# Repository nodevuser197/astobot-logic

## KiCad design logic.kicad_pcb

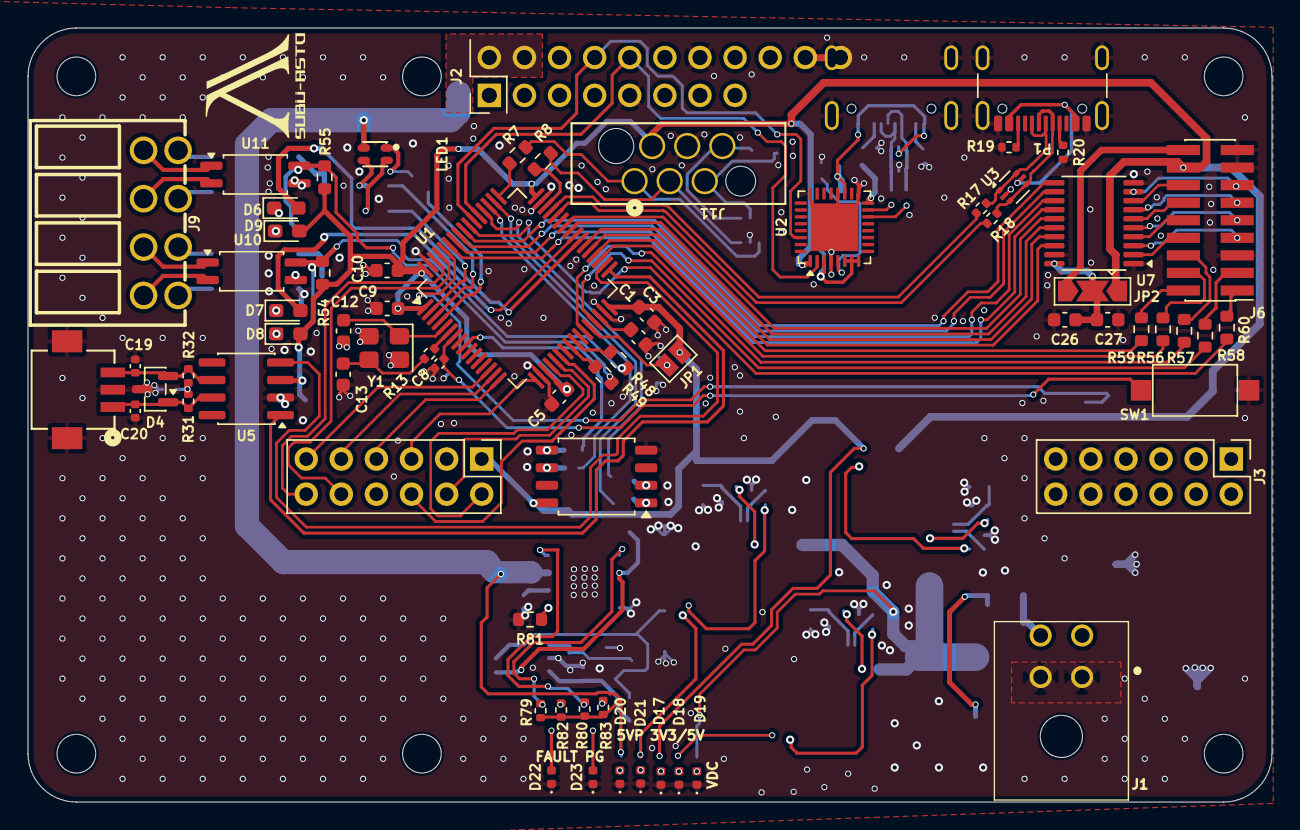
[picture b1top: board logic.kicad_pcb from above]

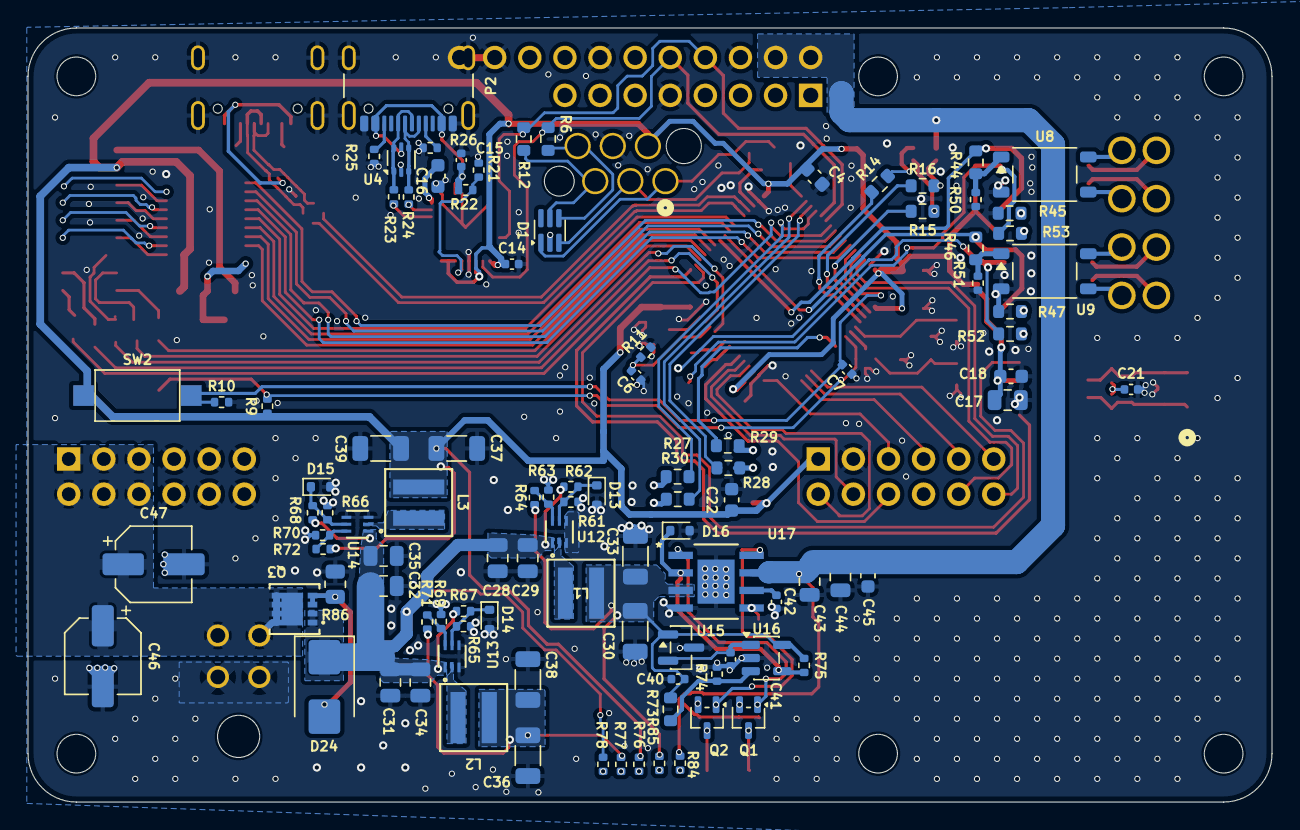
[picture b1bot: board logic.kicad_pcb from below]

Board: 2 copper layers, 90.0 x 56.0 mm, 169 parts (100 on the bottom side), 140 nets.

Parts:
C1, C3, C4, C10: 2u2; C_0603_1608Metric
C5, C9, C18, C26: u1; C_0603_1608Metric
C6, C7, C8, C15, C40, C41: u1; C_0402_1005Metric
C12, C13: 15p; C_0603_1608Metric
C14: 1u; C_0402_1005Metric
C16, C22, C27: 1u; C_0603_1608Metric
C17: 2.2u; C_0805_2012Metric
C19, C20: 47p; C_0402_1005Metric
C21: 2u2; C_0402_1005Metric
C28, C31, C32: 15u; C_0805_2012Metric
C29, C34, C35: 6.8u; C_0805_2012Metric
C30, C33, C36, C37, C38, C39: 33u; C_1206_3216Metric
C42: 22n; C_0402_1005Metric
C43, C44: 4u7; C_0805_2012Metric
C45: u22; C_0603_1608Metric
C46: 10u; CP_Elec_5x5.4
C47: 22u; CP_Elec_5x5.4
D1: SP0504BAHT; SOT-363_SC-70-6
D4: TVS-DUAL; SOT-23
D6, D7, D8, D9: Red; LED_0603_1608Metric_Pad1.05x0.95mm_HandSolder
D13, D14, D15: 5.1; D_SOD-523
D16: 5.1V; D_SOD-523
D17, D18: BLUE; LED_0402_1005Metric
D19, D20, D22: RED; LED_0402_1005Metric
D21, D23: GREEN; LED_0402_1005Metric
D24: SMBJ26; D_SMB
J1: CN; 66200421022
J2: Raspberry_Pi_4; PinHeader_2x20_P2.54mm_Vertical
J3: PWR; PinHeader_2x06_P2.54mm_Vertical
J4: Logic; PinHeader_2x06_P2.54mm_Vertical
J5: Conn_01x03; DF13A-3P-1-25H-21-
J6: Conn_02x09_Odd_Even; PinHeader_2x09_P1.27mm_Vertical_SMD
J9: ISI/O; JL15EDGRHC-35004B02
J11: Debug; CONN6_490107670612_WRE
JP1: SJ; SolderJumper-2_P1.3mm_Open_Pad1.0x1.5mm
JP2: SJ; SolderJumper-3_P2.0mm_Open_TrianglePad1.0x1.5mm
L1, L2, L3: 3.3u; IND_EXLA-0402_EAT
LED1: LTST-C19HE1WT_C458749; LTST-C19HE1WT
P1, P2: USB_C_Plug_USB2.0; USB_C_Receptacle_GCT_USB4105-xx-A_16P_TopMnt_Horizontal
Q1, Q2: MMBTA94; SOT-323_SC-70
Q3: DMP2008UFG-7; DMP2008UFG-7_DIO
R6, R7, R8, R12, R27, R28, R29, R30, R48, R49, R56, R57, R58, R59, R60: 33; R_0603_1608Metric
R9, R10, R11, R22, R50, R51, R74, R75, R79, R80: 10k; R_0402_1005Metric
R13: 0; R_0402_1005Metric
R14: 330; R_0603_1608Metric
R15, R16: 180; R_0603_1608Metric
R17, R18, R23, R24: 15; R_0402_1005Metric
R19, R20, R25, R26: 5.1k; R_0402_1005Metric
R21: 15k; R_0402_1005Metric
R31, R32: 60; R_0402_1005Metric
R44, R46: 220; R_0603_1608Metric
R45, R47, R52, R53: 670; R_0603_1608Metric
R54, R55: 10k; R_0603_1608Metric
R61, R63, R65, R66, R69, R70: 30k; R_0402_1005Metric
R62, R67, R68: 20k; R_0402_1005Metric
R64, R71, R72: 220k; R_0402_1005Metric
R73: 10.5k; R_0603_1608Metric
R76, R77, R78, R82, R83, R84, R85: 2k2; R_0402_1005Metric
R81: 91; R_0603_1608Metric
R86: 68k; R_0805_2012Metric
SW1, SW2: SW_SPST; SW_SPST_CK_RS282G05A3
U1: STM32F446RCTx; LQFP-64_10x10mm_P0.5mm
U2: CY7C65213-32LTXI; QFN-32-1EP_5x5mm_P0.5mm_EP3.45x3.45mm
U3, U4: USBLC6-2P6; SOT-666
U5: SN65HVD232; SOIC-8_3.9x4.9mm_P1.27mm
U6: W25Q16JVSS; SOIC-8_5.3x5.3mm_P1.27mm
U7: 74AHC541; TSSOP-20_4.4x6.5mm_P0.65mm
U8, U9: TLP175A; Toshiba_SOIC-4-6_4.4x3.6mm_P1.27mm
U10, U11: FODM217A; SOP-4_4.4x2.6mm_P1.27mm
U12, U13, U14: TPS565247DRLR; SOT5X3-6_DRL_TEX
U15: REF3025; SOT-23
U16: LM397; SOT-23-5
U17: TPS2421-1DDA; DDA8_3P2X2P69
Y1: 12MHz; Crystal_SMD_3225-4Pin_3.2x2.5mm

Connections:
+3V3: C3.1, C4.1, C5.1, C9.1, C10.1, C14.1, C17.1, C18.1, C22.1, C37.1, C39.1, D8.2 (A), D9.2 (A), J4.1, J6.16, J11.2 (+12V), JP1.2 (B), JP2.1 (A), L3.1, R9.1, R54.1, R55.1, R72.2, R76.2, SW2.1 (A), U1.1 (VBAT), U1.19 (VDD), U1.32 (VDD), U1.48 (VDD), U1.64 (VDD), U2.1 (VCCIO), U2.3 (RI), U2.6 (DSR), U2.7 (DCD), U2.8 (CTS), U5.3 (VCC), U6.8 (VCC)
+5V: C36.1, C38.1, J6.18, JP2.3 (B), L2.1, R71.2, R77.2
+5VP: C30.1, C33.1, C40.1, L1.1, R64.2, R73.1, R75.1, R85.1, U15.1 (IN), U16.5 (V+), U17.3 (VIN)
+BATT: C46.1, C47.1, J1.3, J1.4, J3.1, J3.2, J3.3, J3.4, J3.5, J3.6, Q3.5, Q3.6, Q3.7, Q3.8
/1A: J6.8, U7.2 (A0)
/1B: J6.12, U7.6 (A4)
/2A: J6.7, U7.3 (A1)
/2B: J6.11, U7.7 (A5)
/3A: J6.10, U7.4 (A2)
/3B: J6.14, U7.8 (A6)
/4A: J6.9, U7.5 (A3)
/4B: J6.13, U7.9 (A7)
/CLK: J6.3, R58.2
/I2C.DATA: J6.1, R60.2
/Isolated IO/INCH1: J9.3, U8.4
/Isolated IO/INCH2: J9.7, U9.4
/Isolated IO/IsolatedInput1/POUT: R49.2, R53.2, R55.2, U11.4
/Isolated IO/IsolatedInput/POUT: R48.2, R52.2, R54.2, U10.4
/Isolated IO/IsolatedOutput1/PIN: R46.2, R51.1, U9.1
/Isolated IO/IsolatedOutput/PIN: R44.2, R50.1, U8.1
/Isolated IO/OUTCH1: J9.1, U8.6
/Isolated IO/OUTCH2: J9.5, U9.6
/Isolated IO/PCH1: J9.6, U10.1
/Isolated IO/PCH2: J9.2, U11.1
/Isolated IO/REFCH1: J9.8, U10.2
/Isolated IO/REFCH2: J9.4, U11.2
/Periphals/CANH: C20.1, D4.1 (K1), J5.1, R31.2, U5.7 (CANH)
/Periphals/CANL: C19.1, D4.2 (K2), J5.3, R32.1, U5.6 (CANL)
/Periphals/DN: R24.1, U2.15 (USBDM)
/Periphals/DP: R23.1, U2.14 (USBDP)
/Periphals/_DN: P2.A7 (D-), P2.B7 (D-), R24.2, U4.3 (I/O2), U4.4 (I/O2)
/Periphals/_DP: P2.A6 (D+), P2.B6 (D+), R23.2, U4.1 (I/O1), U4.6 (I/O1)
/Periphals/uDN: P1.A7 (D-), P1.B7 (D-), R18.2, U3.3 (I/O2), U3.4 (I/O2)
/Periphals/uDP: P1.A6 (D+), P1.B6 (D+), R17.2, U3.1 (I/O1), U3.6 (I/O1)
/Power/~FAULT: Q1.1 (B), R79.2, U17.1 (~FLT)
/Power/~PG: Q2.1 (B), R80.2, U17.8 (~PG)
/SPI.CS: J6.6, R57.2
/SPI.SI: J6.2, R59.2
/SPI.SO: J6.4, R56.2
/uC/BOOT0: C7.1, R10.1, SW2.2 (B), U1.60 (BOOT0)
/uC/BOOT1: C6.1, JP1.1 (A), R11.1, U1.28 (PB2)
/uC/CAN.RX: U1.33 (PB12), U5.1 (D)
/uC/CAN.TX: U1.34 (PB13), U5.4 (R)
/uC/HSE_IN: C12.1, U1.5 (PH0), Y1.1
/uC/HSE_OUT: R13.1, U1.6 (PH1)
/uC/I2C1.CK: J4.12, U1.62 (PB9)
/uC/I2C1.SD: J4.10, U1.61 (PB8)
/uC/I2C2.CK: R58.1, U1.29 (PB10)
/uC/I2C2.SD: R60.1, U1.55 (PB3)
/uC/IO1: R15.2, U1.2 (PC13)
/uC/IO2: R16.2, U1.3 (PC14)
/uC/IO3: R14.2, U1.4 (PC15)
/uC/ISI1: R48.1, U1.25 (PC5)
/uC/ISI2: R49.1, U1.24 (PC4)
/uC/ISO1: D6.2 (A), R44.1, U1.39 (PC8)
/uC/ISO2: D7.2 (A), R46.1, U1.40 (PC9)
/uC/MC.CK: J4.4, U1.21 (PA5)
/uC/MC.CS: J4.2, U1.20 (PA4)
/uC/MC.SI: J4.6, U1.22 (PA6)
/uC/MC.SO: J4.8, U1.23 (PA7)
/uC/MCP1: J4.11, U1.14 (PA0)
/uC/MCP2: J4.9, U1.15 (PA1)
/uC/MCP3: J4.7, U1.16 (PA2)
/uC/MCP4: J4.5, U1.17 (PA3)
/uC/NRST: C8.1, R9.2, SW1.1 (A), U1.7 (NRST)
/uC/QEA1: U1.41 (PA8), U7.16 (Y2)
/uC/QEA2: U1.56 (PB4), U7.11 (Y7)
/uC/QEA3: U1.58 (PB6), U7.13 (Y5)
/uC/QEA4: U1.37 (PC6), U7.18 (Y0)
/uC/QEB1: U1.42 (PA9), U7.15 (Y3)
/uC/QEB2: U1.57 (PB5), U7.12 (Y6)
/uC/QEB3: U1.59 (PB7), U7.14 (Y4)
/uC/QEB4: U1.38 (PC7), U7.17 (Y1)
/uC/SI2.CS: R57.1, U1.27 (PB1)
/uC/SI2.SI: R59.1, U1.36 (PB15)
/uC/SI2.SO: R56.1, U1.35 (PB14)
/uC/SI3.CK: R28.1, U1.51 (PC10)
/uC/SI3.CS: R27.1, U1.50 (PA15)
/uC/SI3.SI: R29.1, U1.9 (PC1)
/uC/SI3.SO: R30.1, U1.52 (PC11)
/uC/SWD.CK: R7.1, U1.49 (PA14)
/uC/SWD.IO: R8.1, U1.46 (PA13)
/uC/UART.RX: J2.8 (GPIO14/UART_TXD), R12.1, U1.54 (PD2), U2.30 (TXD)
/uC/UART.TX: J2.10 (GPIO15/UART_RXD), R6.2, U1.53 (PC12), U2.2 (RXD)
/uC/USB.DN: R18.1, U1.44 (PA11)
/uC/USB.DP: R17.1, U1.45 (PA12)
GND: C1.2, C3.2, C4.2, C5.2, C6.2, C7.2, C8.2, C9.2, C10.2, C12.2, C13.2, C14.2, C15.2, C16.2, C17.2, C18.2, C19.2, C20.2, C21.2, C22.2, C26.2, C27.2, C28.2, C29.2, C30.2, C31.2, C32.2, C33.2, C34.2, C35.2, C36.2, C37.2, C38.2, C39.2, C40.2, C41.2, C42.2, C43.2, C44.2, C45.2, C46.2, C47.2, D1.2 (A), D4.3 (A), D13.2 (A), D14.2 (A), D15.2 (A), D16.2 (A), D17.1 (K), D18.1 (K), D19.1 (K), D20.1 (K), D21.1 (K), D22.1 (K), D23.1 (K), J1.1, J1.2, J2.6 (GND), J2.9 (GND), J2.14 (GND), J2.20 (GND), J3.7, J3.8, J3.9, J3.10, J3.11, J3.12, J4.3, J5.2, J6.5, J6.15, J6.17, J11.4 (GND), P1.A1 (GND), P1.A12 (GND), P1.B1 (GND), P1.B12 (GND), P1.S1 (SHIELD), P2.A1 (GND), P2.A12 (GND), P2.B1 (GND), P2.B12 (GND), P2.S1 (SHIELD), R10.2, R11.2, R19.2, R20.2, R21.2, R25.2, R26.2, R45.2, R47.2, R50.2, R51.2, R61.2, R63.1, R65.2, R66.2, R69.1, R70.1, R74.2, R81.2, R86.2, SW1.2 (B), U1.18 (VSS), U1.31 (VSS), U1.47 (VSS), U1.63 (VSS), U2.4 (GND), U2.17 (GND), U2.20 (GND), U2.24 (AGND), U2.33 (1EP), U3.2 (GND), U4.2 (GND), U5.2 (GND), U6.4 (GND), U7.1 (G1), U7.10 (GND), U7.19 (G2), U8.3, U9.3, U10.3, U11.3, U12.3 (GND), U12.4 (AGND), U13.3 (GND), U13.4 (AGND), U14.3 (GND), U14.4 (AGND), U15.3 (GND), U16.2 (V-), U17.4 (GND), U17.EPAD, Y1.2, Y1.4
HL5V: C43.1, C44.1, C45.1, J2.2 (5V), J2.4 (5V), LED1.4 (+), R79.1, R80.1, R82.1, R83.2, R84.2, U17.7 (VOUT)
unnamed: C13.1, R13.2, Y1.3
unnamed: C21.1, R31.1, R32.2
unnamed: D1.1 (K), J11.1 (+12V), R7.2
unnamed: D1.3 (K), J11.3 (GND), R8.2
unnamed: D1.4 (K), J11.6 (GND), R6.1
unnamed: D1.5 (K), J11.5 (GND), R12.2
unnamed: D6.1 (K), R45.1
unnamed: D7.1 (K), R47.1
unnamed: D8.1 (K), R52.1
unnamed: D9.1 (K), R53.1
unnamed: D13.1 (K), R61.1, R62.2, U12.5 (EN)
unnamed: D14.1 (K), R65.1, R67.2, U13.5 (EN)
unnamed: D15.1 (K), R66.1, R68.2, U14.5 (EN)
unnamed: D16.1 (K), R75.2, U16.4, U17.2 (~EN)
unnamed: D17.2 (A), R76.1
unnamed: D18.2 (A), R77.1
unnamed: D19.2 (A), R78.2
unnamed: D20.2 (A), R84.1
unnamed: D21.2 (A), R85.2
unnamed: D22.2 (A), Q1.3 (C)
unnamed: D23.2 (A), Q2.3 (C)
unnamed: D24.2 (A), Q3.3, Q3.4, R86.1
unnamed: C26.1, C27.1, JP2.2 (C), U7.20 (VCC)
unnamed: LED1.3 (B-), R16.1
unnamed: LED1.2 (G-), R15.1
unnamed: LED1.1 (R-), R14.1
unnamed: P1.A5 (CC), R20.1
unnamed: P1.B5 (VCONN), R19.1
unnamed: P2.A5 (CC), R26.1
unnamed: P2.B5 (VCONN), R25.1
unnamed: Q1.2 (E), R82.2
unnamed: Q2.2 (E), R83.1
unnamed: C1.1, U1.30 (VCAP_1)
unnamed: R21.1, R22.1, U2.5 (GPIO5)
unnamed: C16.1, U2.16 (VCCD)
unnamed: R28.2, U6.6 (CLK)
unnamed: R29.2, U6.5 (DI/IO_{0})
unnamed: R30.2, U6.2 (DO/IO_{1})
unnamed: R27.2, U6.1 (~CS)
unnamed: R63.2, R64.1, U12.6 (FB)
unnamed: L1.2, U12.2 (SW)
unnamed: R69.2, R71.1, U13.6 (FB)
unnamed: L2.2, U13.2 (SW)
unnamed: R70.2, R72.1, U14.6 (FB)
unnamed: L3.2, U14.2 (SW)
unnamed: C41.1, U15.2 (OUT), U16.1 (-)
unnamed: R73.2, R74.1, U16.3 (+)
unnamed: C42.1, U17.6 (CT)
unnamed: R81.1, U17.5 (ISET)
VBUS1: P1.A4 (VBUS), P1.A9 (VBUS), P1.B4 (VBUS), P1.B9 (VBUS), U3.5 (VBUS)
VBUS2: C15.1, P2.A4 (VBUS), P2.A9 (VBUS), P2.B4 (VBUS), P2.B9 (VBUS), R22.2, U2.19 (VCC), U4.5 (VBUS)
VDC: C28.1, C29.1, C31.1, C32.1, C34.1, C35.1, D24.1 (K), Q3.1, Q3.2, R62.1, R67.1, R68.1, R78.1, U12.1 (VIN), U13.1 (VIN), U14.1 (VIN)
